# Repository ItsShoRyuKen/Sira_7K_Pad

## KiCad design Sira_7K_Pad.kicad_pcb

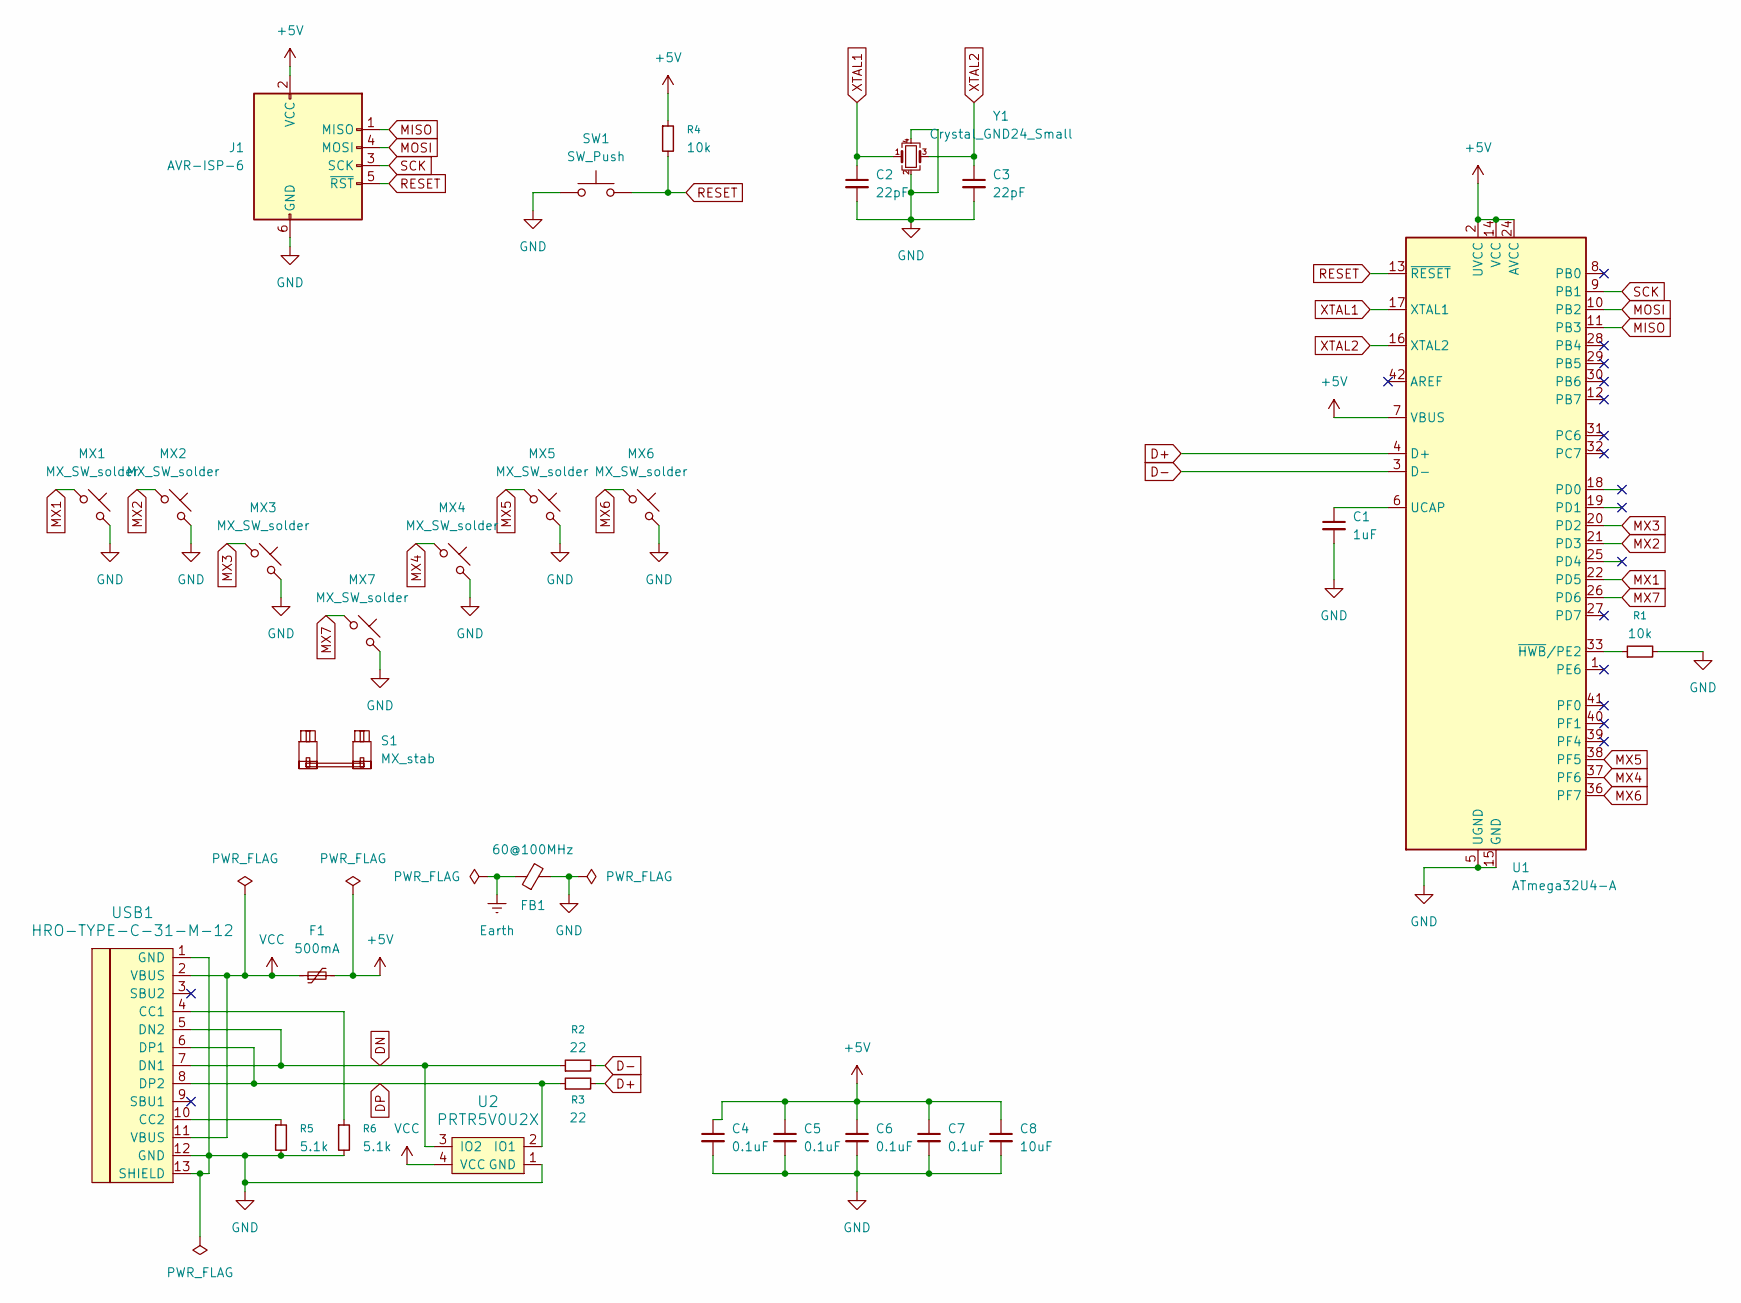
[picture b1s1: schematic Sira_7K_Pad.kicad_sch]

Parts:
C1: 1uF; C_0805_2012Metric_Pad1.18x1.45mm_HandSolder
C2, C3: 22pF; C_0805_2012Metric_Pad1.18x1.45mm_HandSolder
C4, C5, C6, C7: 0.1uF; C_0805_2012Metric_Pad1.18x1.45mm_HandSolder
C8: 10uF; C_0805_2012Metric_Pad1.18x1.45mm_HandSolder
F1: 500mA; Fuse_1206_3216Metric_Pad1.42x1.75mm_HandSolder
FB1: 60@100MHz; L_0805_2012Metric_Pad1.05x1.20mm_HandSolder
J1: AVR-ISP-6; Reset_Pretty-Mask
MX1, MX2, MX3, MX4, MX5, MX6, MX7: MX_SW_solder; SW_MX_1u
R1, R4: 10k; R_0805_2012Metric_Pad1.20x1.40mm_HandSolder
R2, R3: 22; R_0805_2012Metric_Pad1.20x1.40mm_HandSolder
R5, R6: 5.1k; R_0805_2012Metric_Pad1.20x1.40mm_HandSolder
S1: MX_stab; STAB_MX_P_6.25u
SW1: SW_Push; SW_SPST_SKQG_WithStem
U1: ATmega32U4-A; TQFP-44_10x10mm_P0.8mm
U2: PRTR5V0U2X; SOT143B
USB1: HRO-TYPE-C-31-M-12; HRO-TYPE-C-31-M-12-HandSoldering
Y1: Crystal_GND24_Small; Crystal_SMD_3225-4Pin_3.2x2.5mm_HandSoldering

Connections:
+5V: C4.1, C5.1, C6.1, C7.1, C8.1, F1.2, J1.2 (VCC), R4.1, U1.2 (UVCC), U1.7 (VBUS), U1.14 (VCC), U1.24 (AVCC), U1.34 (VCC), U1.44 (AVCC)
D+: R3.2, U1.4 (D+)
D-: R2.2, U1.3 (D-)
DN: R2.1, U2.3 (IO2), USB1.5 (DN2), USB1.7 (DN1)
DP: R3.1, U2.2 (IO1), USB1.6 (DP1), USB1.8 (DP2)
Earth: FB1.1
GND: C1.2, C2.2, C3.2, C4.2, C5.2, C6.2, C7.2, C8.2, FB1.2, J1.6 (GND), MX1.2, MX2.2, MX3.2, MX4.2, MX5.2, MX6.2, MX7.2, R1.2, R5.2, R6.2, SW1.1, U1.5 (UGND), U1.15 (GND), U1.23 (GND), U1.35 (GND), U1.43 (GND), U2.1 (GND), USB1.1 (GND), USB1.12 (GND), USB1.13 (SHIELD), Y1.2, Y1.4
MISO: J1.1 (MISO), U1.11 (PB3)
MOSI: J1.4 (MOSI), U1.10 (PB2)
MX1: MX1.1, U1.22 (PD5)
MX2: MX2.1, U1.21 (PD3)
MX3: MX3.1, U1.20 (PD2)
MX4: MX4.1, U1.37 (PF6)
MX5: MX5.1, U1.38 (PF5)
MX6: MX6.1, U1.36 (PF7)
MX7: MX7.1, U1.26 (PD6)
unnamed: C1.1, U1.6 (UCAP)
unnamed: R1.1, U1.33 (~HWB/PE2)
unnamed: R6.1, USB1.4 (CC1)
unnamed: R5.1, USB1.10 (CC2)
RESET: J1.5 (~RST), R4.2, SW1.2, U1.13 (~RESET)
SCK: J1.3 (SCK), U1.9 (PB1)
VCC: F1.1, U2.4 (VCC), USB1.2 (VBUS), USB1.11 (VBUS)
XTAL1: C2.1, U1.17 (XTAL1), Y1.1
XTAL2: C3.1, U1.16 (XTAL2), Y1.3

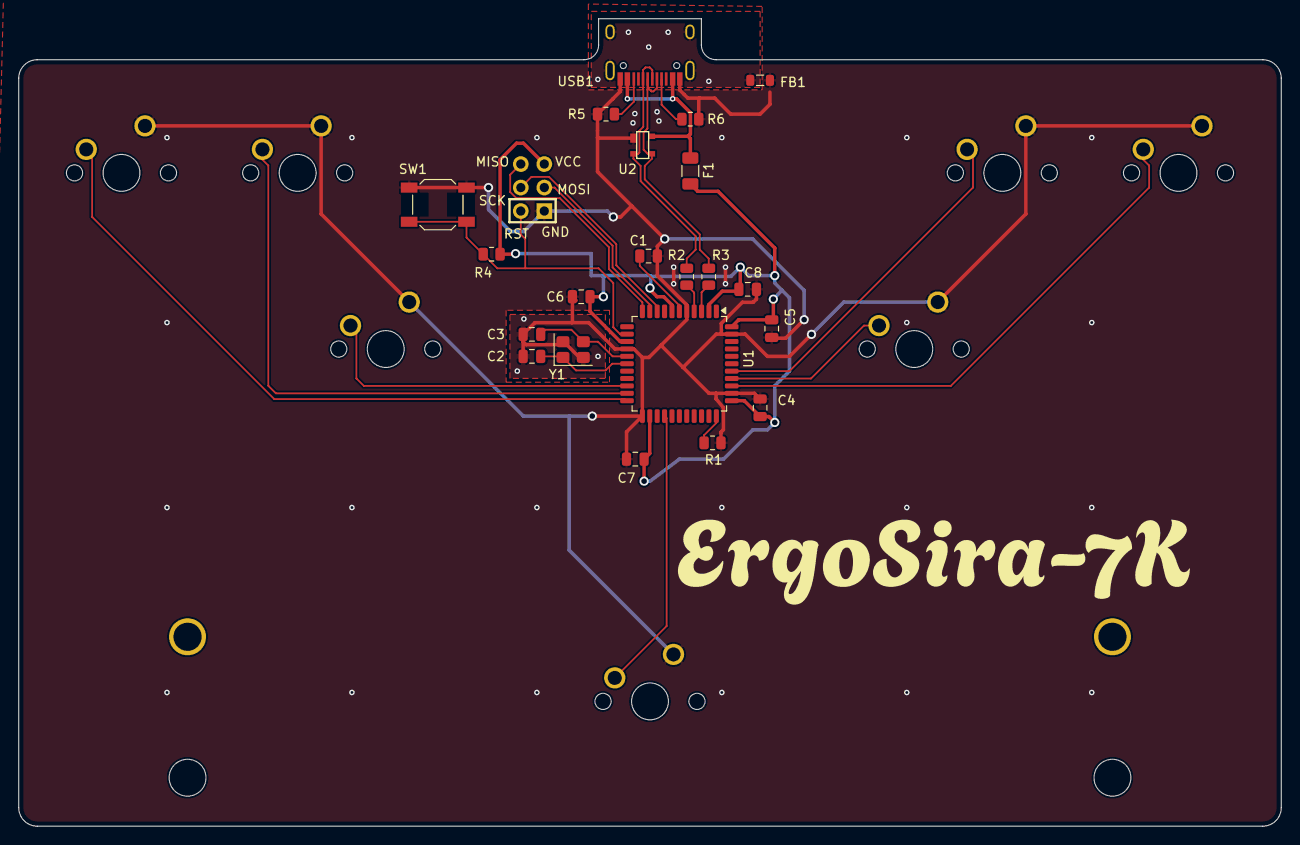
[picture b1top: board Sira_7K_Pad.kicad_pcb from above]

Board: 2 copper layers, 136.5 x 87.3 mm, 30 parts (0 on the bottom side), 24 nets.

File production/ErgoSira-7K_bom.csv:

Designator,Footprint,Quantity,Value,LCSC Part #
C1,0805,1,1uF,
"C2, C3",0805,2,22pF,
"C4, C5, C6, C7",0805,4,0.1uF,
C8,0805,1,10uF,
F1,1206,1,500mA,
FB1,0805,1,60@100MHz,
J1,Reset_Pretty-Mask,1,AVR-ISP-6,
"MX1, MX2, MX3, MX4, MX5, MX6, MX7",SW_MX_1u,7,MX_SW_solder,
"R1, R4",0805,2,10k,
"R2, R3",0805,2,22,
"R5, R6",0805,2,5.1k,
S1,STAB_MX_P_6.25u,1,MX_stab,
SW1,SW_SPST_SKQG_WithStem,1,SW_Push,
U1,TQFP-44_10x10mm_P0.8mm,1,ATmega32U4-A,
U2,SOT143B,1,PRTR5V0U2X,
USB1,HRO-TYPE-C-31-M-12-Assembly,1,HRO-TYPE-C-31-M-12,
Y1,Crystal_SMD_3225-4Pin_3.2x2.5mm,1,Crystal_GND24_Small,

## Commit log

2025-12-28 added project files
2025-12-28 added libraries
2025-12-28 added libraries to the project preferences
2025-12-28 added usb c libraries
2025-12-28 finished schematic
2025-12-28 finished mcu schematic again
2025-12-29 started pcb layout
2026-01-04 almost finished routing and cleaning up the pcb
2026-01-04 finished (first version) pbc
2026-01-04 deleted older manual backup files
2026-01-04 Fixed clearence error
2026-01-04 Fixed incorrect decoupling capacitors routing
2026-01-04 Moved decoupling capacitor outside of crystal ground zone
2026-01-04 cleanup
